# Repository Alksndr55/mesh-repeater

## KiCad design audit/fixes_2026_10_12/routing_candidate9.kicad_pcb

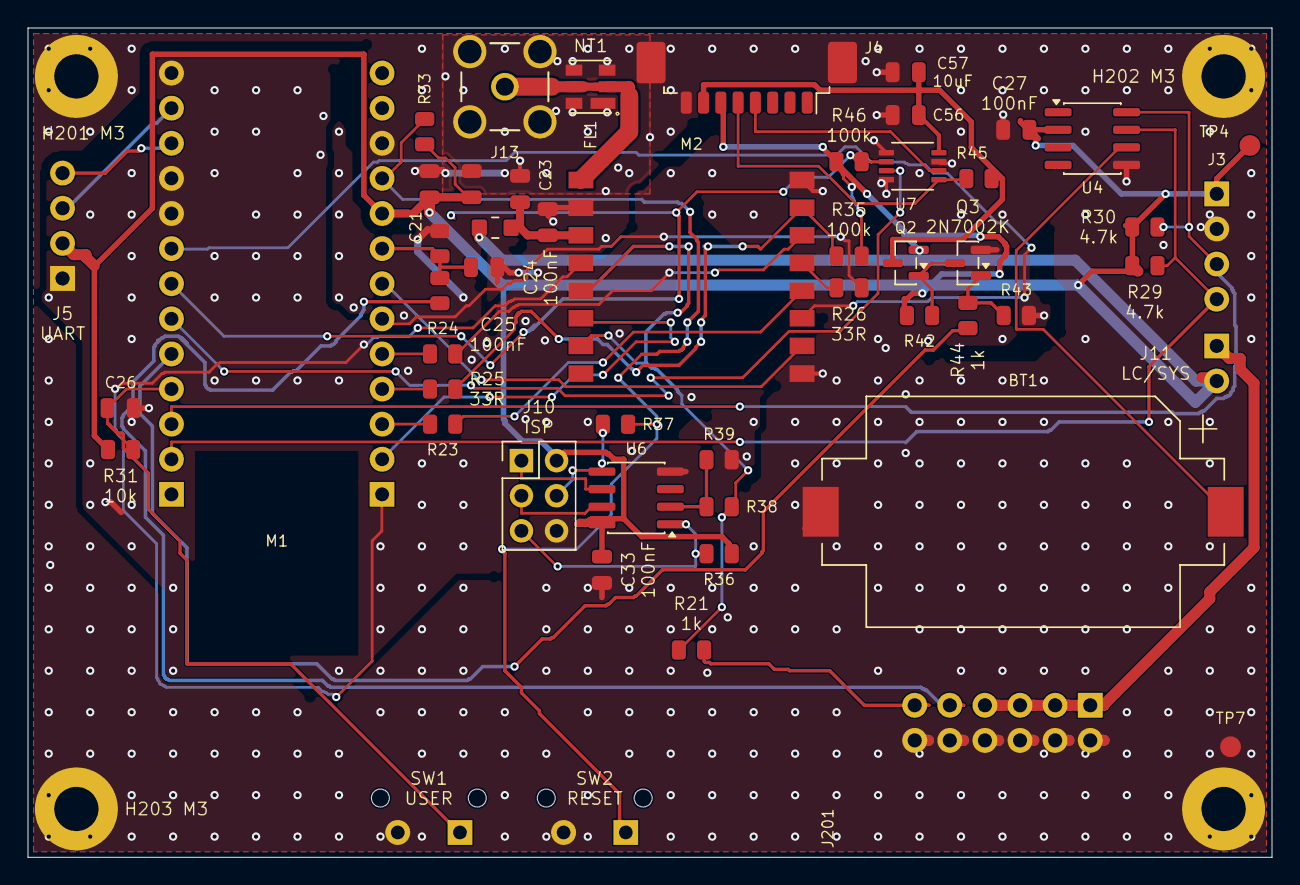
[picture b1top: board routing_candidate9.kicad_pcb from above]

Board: 2 copper layers, 90.0 x 60.0 mm, 57 parts (0 on the bottom side), 42 nets.

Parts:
BT1: CR2032 / holder; BatteryHolder_Keystone_1060_1x2032__V2_BT1
C21: 10uF 16V X7R; C_0805_2012Metric__V2_C21
C22: 100nF 50V X7R; C_0805_2012Metric__V2_C22
C23: 22uF 25V X5R; C_0805_2012Metric__V2_C23
C24: 100nF 50V X7R; C_0805_2012Metric__V2_C24
C25: 100nF 50V X7R; C_0805_2012Metric__V2_C25
C26: 100nF 50V X7R; C_0805_2012Metric__V2_C26
C27: 100nF 50V X7R; C_0805_2012Metric__V2_C27
C33: 100nF 50V X7R; C_0805_2012Metric__V2_C33
C56: 100nF 50V X7R; C_0805_2012Metric__V2_C56
C57: 10uF 16V X7R; C_0805_2012Metric__V2_C57
FB1: 60R@100MHz / 3A; Ferrite_Murata_BLM21PG__V2_FB1
FL1: S869M000S003; SAW_AEL_DCC6C_S869M000S003__V2_FL1
H201: M3 GND contact; GND_M3_D3.2_OD6__V2_H201
H202: M3 GND contact; GND_M3_D3.2_OD6__V2_H202
H203: M3 GND contact; GND_M3_D3.2_OD6__V2_H203
H204: M3 GND contact; GND_M3_D3.2_OD6__V2_H204
J3: I2C3V3; Connfly_DS1022_1x04RUF11_B_Horizontal__V2_J3
J4: GPS / T114 P3; Molex_PicoBlade_53261-0871_1x08-1MP_P1.25mm_Horizontal__V2_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
J5: UART3V3; Connfly_DS1022_1x04RUF11_B_Horizontal__V2_J5
J10: AVR ISP 3V3; PinHeader_2x03_P2.54mm_Vertical__V2_J10
J11: LC OUT - SYS 3V3; Connfly_DS1022_1x02RUF11_B_Horizontal__V2_J11
J13: SMA 50Ohm; SMA_KLS1_SMA002_B_Horizontal__V2_J13
J201: INTERBOARD 12P; Connfly_DS1013_12RSIB_B_0_Horizontal__V2_J201
M1: NiceNano_CLONE_MODIFIED; NiceNano_13x2_Socket__V2_M1
M2: HT-RA62; HT_RA62__V2_M2
NT1: Cu link / cut for FL1; RF_Cut_Link_0p6__V2_NT1
Q2: AO3401A; SOT-23__V2_Q2
Q3: 2N7002K; SOT-23__V2_Q3
R21: 1k; R_0805_2012Metric__V2_R21
R23: 33R; R_0805_2012Metric__V2_R23
R24: 33R; R_0805_2012Metric__V2_R24
R25: 33R; R_0805_2012Metric__V2_R25
R26: 33R; R_0805_2012Metric__V2_R26
R27: 2.2M 0.1%; R_0805_2012Metric__V2_R27
R28: 2.2M 0.1%; R_0805_2012Metric__V2_R28
R29: 4.7k; R_0805_2012Metric__V2_R29
R30: 4.7k; R_0805_2012Metric__V2_R30
R31: 10k; R_0805_2012Metric__V2_R31
R33: 10k; R_0805_2012Metric__V2_R33
R35: 100k; R_0805_2012Metric__V2_R35
R36: 10k; R_0805_2012Metric__V2_R36
R37: 0R; R_0805_2012Metric__V2_R37
R38: 1k; R_0805_2012Metric__V2_R38
R39: 100k; R_0805_2012Metric__V2_R39
R42: 100k; R_0805_2012Metric__V2_R42
R43: 100k; R_0805_2012Metric__V2_R43
R44: 1k; R_0805_2012Metric__V2_R44
R45: 100k; R_0805_2012Metric__V2_R45
R46: 100k; R_0805_2012Metric__V2_R46
SW1: USER; SW_TE_1825027_2_Side__V2_SW1
SW2: RESET; SW_TE_1825027_2_Side__V2_SW2
TP4: SYS_3V3; TestPoint_Pad_D1.5mm__V2_TP4
TP7: GND; TestPoint_Pad_D1.5mm__V2_TP7
U4: DS3231MZ+TRL; SOIC-8_3.9x4.9mm_P1.27mm__V2_U4
U6: ATtiny13A-SSU; SOIC-8_3.9x4.9mm_P1.27mm__V2_U6
U7: SN74LVC2G125; TI_DCT0008A__V2_U7

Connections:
/2. RTC_IO/GPS_EN_GATE: Q3.1 (G), R43.1, R44.2
/2. RTC_IO/GPS_GATE: Q2.1 (G), Q3.3 (D), R42.2
/2. RTC_IO/RTC_BAT: BT1.1 (+), U4.6 (VBAT)
/ANT_RF: FL1.2 (IN), M2.1 (ANT), NT1.1 (A)
/ANT_SMA: FL1.5 (OUT), J13.1 (SIGNAL), NT1.2 (B)
/RADIO_3V3: C23.1, C24.1, FB1.2, M2.3 (3V3_3)
/RADIO_BUSY: M1.7 (P0.29_/_BUSY), M2.10 (BUSY_10)
/RADIO_DIO1: M1.2 (P0.10_/_DIO1), M2.6 (DIO1_6)
/RADIO_RST: M1.1 (P0.09_/_RADIO_RST), M2.4 (RST_4)
/RADIO_RXEN: M1.21 (P0.17_/_RXEN), M2.11 (RXEN_11)
BAT: J201.9, R27.1
BAT_ADC: C25.1, M1.8 (P0.31_/_BAT_ADC), R27.2, R28.1
FILTER_OUT: J11.1, J201.1, J201.3, J201.5, J201.7
GND: BT1.2 (-), C21.2, C22.2, C23.2, C24.2, C25.2, C26.2, C27.2, C33.2, C56.2, C57.2, FL1.1 (GND), FL1.3 (GND), FL1.4 (GND), FL1.6 (GND), H201.1, H202.1, H203.1, H204.1, J3.2, J4.8 (GND), J4.MP, J5.1, J10.6, J13.2 (GND), J201.2, J201.4, J201.6, J201.8, J201.10, J201.12, M1.11 (GND), M1.22 (GND), M1.23 (GND), M1.26 (GND), M2.2 (GND_2), M2.9 (GND_9), M2.16 (GND_16), Q3.2 (S), R28.2, R39.2, R43.2, SW1.2, SW2.2, TP7.1, U4.5 (GND), U6.4 (GND), U7.1 (~OE1), U7.4 (GND), U7.7 (~OE2)
GPS_3V3: C56.1, C57.1, J4.7 (VCC), Q2.3 (D), R45.1, U7.8 (VCC_GPS)
GPS_EN: M1.18 (P0.24_/_GPS_EN_/_DIGITAL_OUT), R44.1
GPS_RX_EXT: J4.4 (RXD_GPS), U7.6 (1Y_/_GPS_RX)
GPS_RX_MCU: M1.19 (P0.22_/_GPS_RX), U7.3 (2Y_/_MCU_RX)
GPS_TX_EXT: J4.5 (TXD_GPS), R45.2, U7.5 (2A_/_GPS_TX)
GPS_TX_MCU: M1.20 (P0.20_/_GPS_TX), R46.2, U7.2 (1A_/_MCU_TX)
MCU_RESET: M1.10 (RESET), R33.2, R37.2, SW2.1
MODE: J201.11, R21.2
unnamed: M1.6 (P0.02_/_MISO), R26.2
unnamed: M1.3 (P1.11_/_SCK), R23.1
unnamed: M1.4 (P1.13_/_NSS), R25.1
unnamed: M1.5 (P1.15_/_MOSI), R24.1
unnamed: M2.13 (MISO_13), R26.1
unnamed: M2.14 (MOSI_14), R24.2
unnamed: M2.15 (NSS_15), R25.2, R35.2
unnamed: M2.12 (SCK_12), R23.2
unnamed: R38.2, R39.1, U6.2 (PB3_/_TXEN_IN)
RADIO_TXEN: M2.5 (TXEN_=_DIO2_5), M2.7 (DIO2_=_TXEN_7), R21.1, R38.1
SCL: J3.3, M1.16 (P0.11_/_SCL), R30.2, U4.8 (SCL)
SDA: J3.4, M1.15 (P1.04_/_SDA), R29.2, U4.7 (SDA)
SYS_3V3: C21.1, C22.1, C27.1, C33.1, FB1.1, J3.1, J4.6 (V_BCKP), J5.2, J10.2, J11.2, M1.9 (VCC_/_MOD_3V3), Q2.2 (S), R29.1, R30.1, R31.1, R33.1, R35.1, R36.1, R42.1, R46.1, TP4.1, U4.2 (VCC), U6.8 (VCC)
UART_RX: J5.4, M1.24 (P0.08_/_UART_RX)
UART_TX: J5.3, M1.25 (P0.06_/_UART_TX)
USER_BTN: C26.1, M1.17 (P1.00_/_USER_BTN), R31.2, SW1.1
WDT_MISO: J10.1, U6.6 (PB1_/_MISO)
WDT_MOSI_RESET: J10.4, R37.1, U6.5 (PB0_/_RESET_OD_/_MOSI)
WDT_RESET: J10.5, R36.2, U6.1 (PB5_/_RESET)
WDT_SCK: J10.3, U6.7 (PB2_/_SCK)

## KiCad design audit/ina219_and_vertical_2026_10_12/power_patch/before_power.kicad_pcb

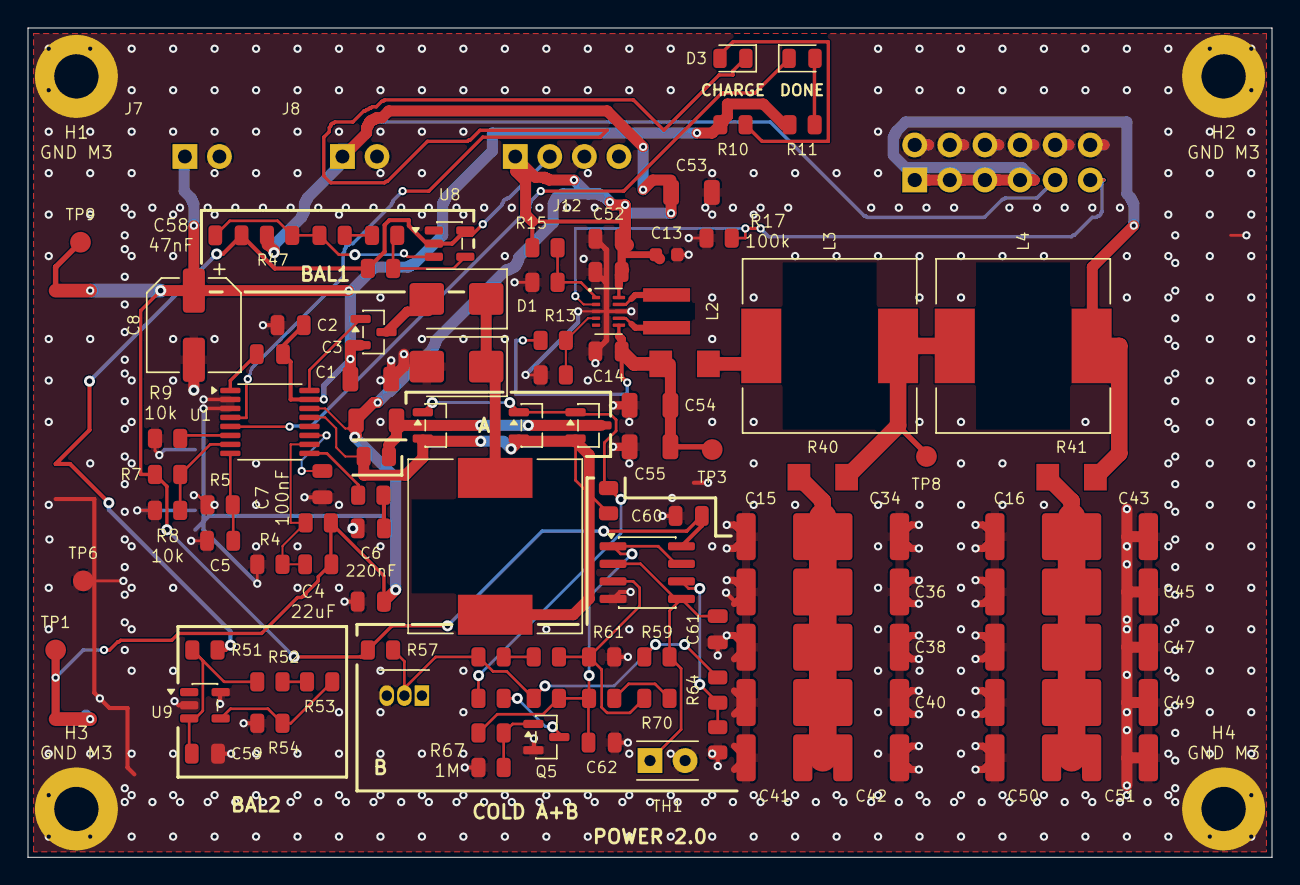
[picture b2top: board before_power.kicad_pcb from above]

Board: 2 copper layers, 90.0 x 60.0 mm, 115 parts (0 on the bottom side), 48 nets.

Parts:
C1: 10uF 50V X7R; C_1206_3216Metric__V2_C1
C2: 100nF 50V X7R; C_0805_2012Metric__V2_C2
C3: 100nF 50V X7R; C_0805_2012Metric__V2_C3
C4: 22uF 25V X5R; C_0805_2012Metric__V2_C4
C5: 470pF 50V C0G; C_0805_2012Metric__V2_C5
C6: 220nF 50V X7R; C_0805_2012Metric__V2_C6
C7: 100nF 50V X7R; C_0805_2012Metric__V2_C7
C8: 47uF 35V; CP_Elec_Panasonic_FK_D_6.3x5.8__V2_C8
C12: 10uF 16V X7R; C_0805_2012Metric__V2_C12
C13: 100nF 50V X7R; C_0603_1608Metric__V2_C13
C14: 22uF 25V X5R; C_0805_2012Metric__V2_C14
C15: 100uF; C_1812_4532Metric__V2_C15
C16: 100uF; C_1812_4532Metric__V2_C16
C30: 12pF 50V C0G; C_0805_2012Metric__V2_C30
C34: 100uF; C_1812_4532Metric__V2_C34
C35: 100uF; C_1812_4532Metric__V2_C35
C36: 100uF; C_1812_4532Metric__V2_C36
C37: 100uF; C_1812_4532Metric__V2_C37
C38: 100uF; C_1812_4532Metric__V2_C38
C39: 100uF; C_1812_4532Metric__V2_C39
C40: 100uF; C_1812_4532Metric__V2_C40
C41: 100uF; C_1812_4532Metric__V2_C41
C42: 100uF; C_1812_4532Metric__V2_C42
C43: 100uF; C_1812_4532Metric__V2_C43
C44: 100uF; C_1812_4532Metric__V2_C44
C45: 100uF; C_1812_4532Metric__V2_C45
C46: 100uF; C_1812_4532Metric__V2_C46
C47: 100uF; C_1812_4532Metric__V2_C47
C48: 100uF; C_1812_4532Metric__V2_C48
C49: 100uF; C_1812_4532Metric__V2_C49
C50: 100uF; C_1812_4532Metric__V2_C50
C51: 100uF; C_1812_4532Metric__V2_C51
C52: 10uF 16V X7R; C_0805_2012Metric__V2_C52
C53: DNP; C_1206_3216Metric__V2_C53
C54: DNP; C_1206_3216Metric__V2_C54
C55: DNP; C_1206_3216Metric__V2_C55
C58: 47nF 16V X7R; C_0805_2012Metric__V2_C58
C59: 47nF 16V X7R; C_0805_2012Metric__V2_C59
C60: 100nF 100V X7R; C_0805_2012Metric__V2_C60
C61: 1nF 100V C0G; C_0805_2012Metric__V2_C61
C62: 100nF 100V X7R; C_0805_2012Metric__V2_C62
D1: SS24; D_SMB__V2_D1
D2: SS24; D_SMB__V2_D2
D3: RED; LED_0805_2012Metric__V2_D3
D4: GREEN; LED_0805_2012Metric__V2_D4
H1: M3 GND contact; GND_M3_D3.2_OD6__V2_H1
H2: M3 GND contact; GND_M3_D3.2_OD6__V2_H2
H3: M3 GND contact; GND_M3_D3.2_OD6__V2_H3
H4: M3 GND contact; GND_M3_D3.2_OD6__V2_H4
J7: SOLAR 12V; JST_XH_S2B-XH-A_1x02_P2.50mm_Horizontal__V2_J7
J8: Na-ion 1S; JST_XH_S2B-XH-A_1x02_P2.50mm_Horizontal__V2_J8
J12: LTO 2S + MID -; KLS_XH_L_KLS1_2_50_04_R_Horizontal__V2_J12
J101: INTERBOARD 12P; Connfly_DS1013_12RSIB_B_0_Horizontal__V2_J101
L1: 100uH; L_Sumida_CDRH127_LDNP_101MC__V2_L1
L2: 0.47uH; L_Coilcraft_XGL4020_471MEC__V2_L2
L3: 2.4uH; L_Sumida_CDRH127_LD__V2_L3
L4: 2.4uH; L_Sumida_CDRH127_LD__V2_L4
Q1: AO3401A; SOT-23__V2_Q1
Q4: AO3401A; SOT-23__V2_Q4
Q5: BSS138; SOT-23__V2_Q5
Q6: AO3401A; SOT-23__V2_Q6
Q7: AO3401A; SOT-23__V2_Q7
R1: 0.28R 1%; R_1206_3216Metric__V2_R1
R3: 61.9k 0.1% <=25ppm/C; R_0805_2012Metric__V2_R3
R4: 100k 0.1% <=25ppm/C; R_0805_2012Metric__V2_R4
R5: 1M 0.1%; R_0805_2012Metric__V2_R5
R6: 120R; R_0805_2012Metric__V2_R6
R7: 105k 0.1%; R_0805_2012Metric__V2_R7
R8: 10k 0.1%; R_0805_2012Metric__V2_R8
R9: 10k; R_0805_2012Metric__V2_R9
R10: 10k; R_0805_2012Metric__V2_R10
R11: 10k; R_0805_2012Metric__V2_R11
R13: 56k 0.1%; R_0805_2012Metric__V2_R13
R14: 10k 0.1%; R_0805_2012Metric__V2_R14
R15: 40.2k 0.1%; R_0805_2012Metric__V2_R15
R16: 49.9k 0.1%; R_0805_2012Metric__V2_R16
R17: 100k; R_0805_2012Metric__V2_R17
R40: 22mR 1%; R_Vishay_WSL1206_18__V2_R40
R41: 22mR 1%; R_Vishay_WSL1206_18__V2_R41
R47: 2R 1%; R_0805_2012Metric__V2_R47
R48: 120k 0.1%; R_0805_2012Metric__V2_R48
R49: 2.49k 0.1%; R_0805_2012Metric__V2_R49
R50: 100k 0.1%; R_0805_2012Metric__V2_R50
R51: 2R 1%; R_0805_2012Metric__V2_R51
R52: 120k 0.1%; R_0805_2012Metric__V2_R52
R53: 2.49k 0.1%; R_0805_2012Metric__V2_R53
R54: 100k 0.1%; R_0805_2012Metric__V2_R54
R55: 47mR 1%; R_Vishay_WSL1206_18__V2_R55
R56: 1.8 ohm 1% 0.125W; R_0805_2012Metric__V2_R56
R57: 47k 1% 0.125W; R_0805_2012Metric__V2_R57
R58: 100k 1%; R_0805_2012Metric__V2_R58
R59: 100k 1%; R_0805_2012Metric__V2_R59
R60: 100k 1%; R_0805_2012Metric__V2_R60
R61: 100k 1%; R_0805_2012Metric__V2_R61
R62: 1M 1%; R_0805_2012Metric__V2_R62
R63: 100k 1%; R_0805_2012Metric__V2_R63
R64: 1.2M 1%; R_0805_2012Metric__V2_R64
R65: 10k 1%; R_0805_2012Metric__V2_R65
R66: 1k 1%; R_0805_2012Metric__V2_R66
R67: 1M 1%; R_0805_2012Metric__V2_R67
R68: 1k 1%; R_0805_2012Metric__V2_R68
R69: 30k 1%; R_0805_2012Metric__V2_R69
R70: 150k 1%; R_0805_2012Metric__V2_R70
TH1: 10k NTC 1% B3988; NTC_TDK_B57861S_Onboard_or_Remote_P2.54mm__V2_TH1
TP1: BAT; TestPoint_Pad_D1.5mm__V2_TP1
TP3: SYS_PRE; TestPoint_Pad_D1.5mm__V2_TP3
TP6: GND; TestPoint_Pad_D1.5mm__V2_TP6
TP8: FILTER_MID; TestPoint_Pad_D1.5mm__V2_TP8
TP9: SOLAR; TestPoint_Pad_D1.5mm__V2_TP9
U1: CN3722; TSSOP-16_4.4x5mm_P0.65mm__V2_U1
U2: TPS63802DLAR; TPS63802_DLA0010A__V2_U2
U8: LMV431A; SOT-23-5__V2_U8
U9: LMV431A; SOT-23-5__V2_U9
U10: LM393XK; SOIC-8_3.9x4.9mm_P1.27mm__V2_U10
U11: LM285Z-2.5G; TO-92_Inline__V2_U11

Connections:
/2. Converter/EN_UV: R15.2, R16.1, U2.1 (EN)
/2. Converter/FB_SYS: R13.2, R14.1, U2.4 (FB)
/2. Converter/FILTER_MID: L3.2, L4.1, R40.1, TP8.1
/2. Converter/LX1: L2.1, U2.9 (L1)
/2. Converter/LX2: L2.2, U2.7 (L2)
/2. Converter/SYS_LC_IN: L3.1, R55.2
/2. Converter/SYS_PRE: C14.1, C54.1, C55.1, R13.1, R55.1, TP3.1, U2.6 (VOUT)
/4. Thermal/CHG_G_ENABLE: Q5.1, R66.2, R67.1
/4. Thermal/CHG_HYST_MID: R62.2, R70.1
/4. Thermal/CHG_PULLDOWN: Q5.3, R68.2
/4. Thermal/CHG_TSENSE: C61.1, R59.2, TH1.1, U10.2, U10.5
/4. Thermal/CHG_VREF: R57.2, R59.1, R60.1, R63.1, R64.1, U11.2
/4. Thermal/CHG_VSHORT: R64.2, R65.1, U10.6
/4. Thermal/CHG_VTH: R61.1, R69.2, R70.2, U10.3
/4. Thermal/CHG_VTH_UP: R60.2, R69.1
/4. Thermal/CHG_WARM: C62.1, R62.1, R63.2, R66.1, U10.1, U10.7
/GATE: Q1.1 (G), U1.16 (DRV)
BAT: C4.1, C12.1, C13.1, C30.1, C52.1, C53.1, J8.1, J12.1, J101.9, R1.2, R3.1, R15.1, R47.1, TP1.1, U1.14 (BAT), U2.10 (VIN)
CHG_CS_M: Q4.3, Q6.3, Q7.3, R1.1, R56.2
CHG_G_SHUNT: Q4.1, Q6.1, Q7.1, R58.2, R68.1
CHRG: D3.1 (K), U1.4 (CHRG)
CS_P: L1.2, Q4.2, Q6.2, Q7.2, R56.1, R58.1, U1.13 (CSP)
DONE: D4.1 (K), U1.5 (DONE)
FILTER_OUT: J101.1, J101.3, J101.5, J101.7, L4.2, R41.1
GND: C1.2, C2.2, C4.2, C5.2, C6.2, C7.2, C8.2, C12.2, C13.2, C14.2, C15.2, C16.2, C34.2, C35.2, C36.2, C37.2, C38.2, C39.2, C40.2, C41.2, C42.2, C43.2, C44.2, C45.2, C46.2, C47.2, C48.2, C49.2, C50.2, C51.2, C52.2, C53.2, C54.2, C55.2, C59.2, C60.2, C61.2, C62.2, D2.2 (A), H1.1, H2.1, H3.1, H4.1, J7.2, J8.2, J12.3, J101.2, J101.4, J101.6, J101.8, J101.10, J101.12, Q5.2, R4.2, R5.2, R8.2, R9.2, R14.2, R16.2, R17.2, R54.2, R61.2, R65.2, R67.2, TH1.2, TP6.1, U1.2 (PGND), U1.3 (GND), U2.3 (AGND), U2.8 (PGND), U9.2 (A), U9.5 (A), U10.4, U11.3
LTO_MID: C58.2, J12.2, R50.2, R51.1, U8.2 (A), U8.5 (A)
MODE: J101.11, R17.1, U2.2 (MODE)
unnamed: C6.1, R6.2
unnamed: C15.1, C34.1, C35.1, C36.1, C37.1, C38.1, C39.1, C40.1, C41.1, C42.1, R40.2
unnamed: C16.1, C43.1, C44.1, C45.1, C46.1, C47.1, C48.1, C49.1, C50.1, C51.1, R41.2
unnamed: D1.2 (A), Q1.3 (D)
unnamed: D1.1 (K), D2.1 (K), L1.1
unnamed: D3.2 (A), R10.2
unnamed: D4.2 (A), R11.2
unnamed: R48.2, R49.1
unnamed: R52.2, R53.1
unnamed: C5.1, R5.1, U1.8 (COM1)
unnamed: R6.1, U1.9 (COM2)
unnamed: C7.1, U1.11 (COM3)
unnamed: C30.2, R3.2, R4.1, U1.10 (FB)
unnamed: R7.2, R8.1, U1.7 (MPPT)
unnamed: R9.1, U1.6 (TEMP)
unnamed: C3.2, U1.1 (VG)
unnamed: C58.1, R47.2, R48.1, U8.3 (K)
unnamed: R49.2, R50.1, U8.4 (REF)
unnamed: C59.1, R51.2, R52.1, U9.3 (K)
unnamed: R53.2, R54.1, U9.4 (REF)
SOLAR: C1.1, C2.1, C3.1, C8.1, C60.1, J7.1, Q1.2 (S), R7.1, R10.1, R11.1, R57.1, TP9.1, U1.15 (VCC), U10.8
